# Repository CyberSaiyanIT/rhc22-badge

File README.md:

# RHC22 Badge

Cyber Saiyan community has designed and developed a special gadget to celebrate RomHack Camp 2022.

You can play with the badge during MOCA 2024 at Cyber Saiyan Village where we will have 20 badges available. If you have your own badge from RomHack Camp 2022 please bring it with you.
Some useful information
* In order to start playing around with and hacking it, is recommended to bring a micro USB data cable with you
* It is also recommended to bring replacement 1.5V AA batteries and/or a powerbank
* The badge is already flashed with the MOCA specific firmware
* We really will appreciate any improvement to the project and pull requests
* Don't hesitate to come and visit us at the Cyber Saiyan Village if you need help

## Features

The badge has some very simple features that will improve your Camp experience:
* It is designed to recall the dragon spheres (maybe you will be able to summon Shenron too)
* The base SOC is a single core ESP32-C3 
   * Integrates a 32-bit core RISC-V microcontroller with a maximum clock speed of 160 MHz
   * 22 configurable GPIOs
   * 400 KB of internal RAM and 4MB flash
   * WiFi and Bluetooth 5
* In the front there are 7 RGB leds
* In the back you have  
   * Two push buttons; use your nail for a better experience :)
   * A 2.4'' TFT screen 
   * A two AA battery holder

Once powered the badge will be assigned a 1-7 ID and will start to advertise itself using BLE and the screen will show the RomHack Camp 2022 logo 
* You can move to next/prev screen by a 1s long press
* The 1st screen is the RHC22 schedule: 
   * You will be able to read the schedule of the Camp (use the 4th screen to update it)
* The 2nd screen is the badges' radar: 
   * You will see all the badges around you in a dragon ball style
* The 3rd screen is the badge's list: 
   * You will see all the badges around you in a table view
* The 4th screen is for the WiFI functionalities: 
   * Start the AP mode and connect with your PC/smartphone in order to explore more functionalities
   * Start the schedule SYNC mode in order to update the schedule at the 2nd screen
* The 5th screen is for fun (you will be able to play with snake)

# Toolchain setup

## Prepare the environment 

### Visual Studio Code (VSCode)
Install Visual Studio Code as development environment:

* https://code.visualstudio.com/ - follow instructions there, if you don't have vscode yet.

### PlatformIO (PIO) extension
Install PlatformIO extension on Visual Studio Code:

* [Installation](http://docs.platformio.org/page/ide/vscode.html)
* [Quick Start](http://docs.platformio.org/page/ide/vscode.html#quick-start)
* [User Guide](http://docs.platformio.org/page/ide/vscode.html#user-guide)

Please follow to the official documentation [PlatformIO IDE for VSCode](http://docs.platformio.org/page/ide/vscode.html).

## Setup the project

* Git clone this repository and open it on VSCode

If you get the error message "No module named pkg_resources", you need to open the 'PlatformIO Core CLI' and execute command:
   * <span>pip install setuptools</span>

## Build www data (Linux)

* Prerequisites:
   * Install Node.js and NPM
* Use NPM to Install required Packages:
   * npm install node-minify node-sass

* ./www-build.sh

## Build www data (Docker)

* Install docker
* docker build --pull --rm -f "Dockerfile" -t rhc22badge:latest "."
* (Bash) docker run -it -v <span>$</span>(pwd)/public:/public -v <span>$</span>(pwd)/data/www:/output rhc22badge
* (Powershell) docker run -it -v <span>$</span>{PWD}/public:/public -v <span>$</span>{PWD}/data/www:/output rhc22badge
   
## Build/Upload Filesystem

In order to upload the filesystem to the badge you need to plugin the badge using USB.
In the "Project Tasks" view of PIO navigate to:

* RHC22-Bagde
   * Platform
      * Build Filesystem Image
      * Upload Filesystem Image

## Build/Upload Firmware
In order to upload the firmware to the badge you need to plugin the badge using USB.
In the "Project Tasks" view of PIO navigate to:

* RHC22-Bagde
   * General
      * Build
      * Upload

# Known Issues
* after dowloading the MOCA schedule from web you should restart the badge to see the updated schedule. This is due to a memory allocartion problem (the json file is too big) and the fix is a WIP

# Misc

## WiFi SSID name lenght limit

The WiFi SSID name configure to connect to external AP is limited to 20 chars

## Use a different logo image

To use a different logo first you need to 
* convert the BMP/JPG/PNG/SVG file to a C array; you can do this using an [online image converter](https://lvgl.io/tools/imageconverter) setting CF_TRUE_COLOR_ALPHA option
* adjust [main/badge/common/img_logo.c](main/badge/common/img_logo.c) file

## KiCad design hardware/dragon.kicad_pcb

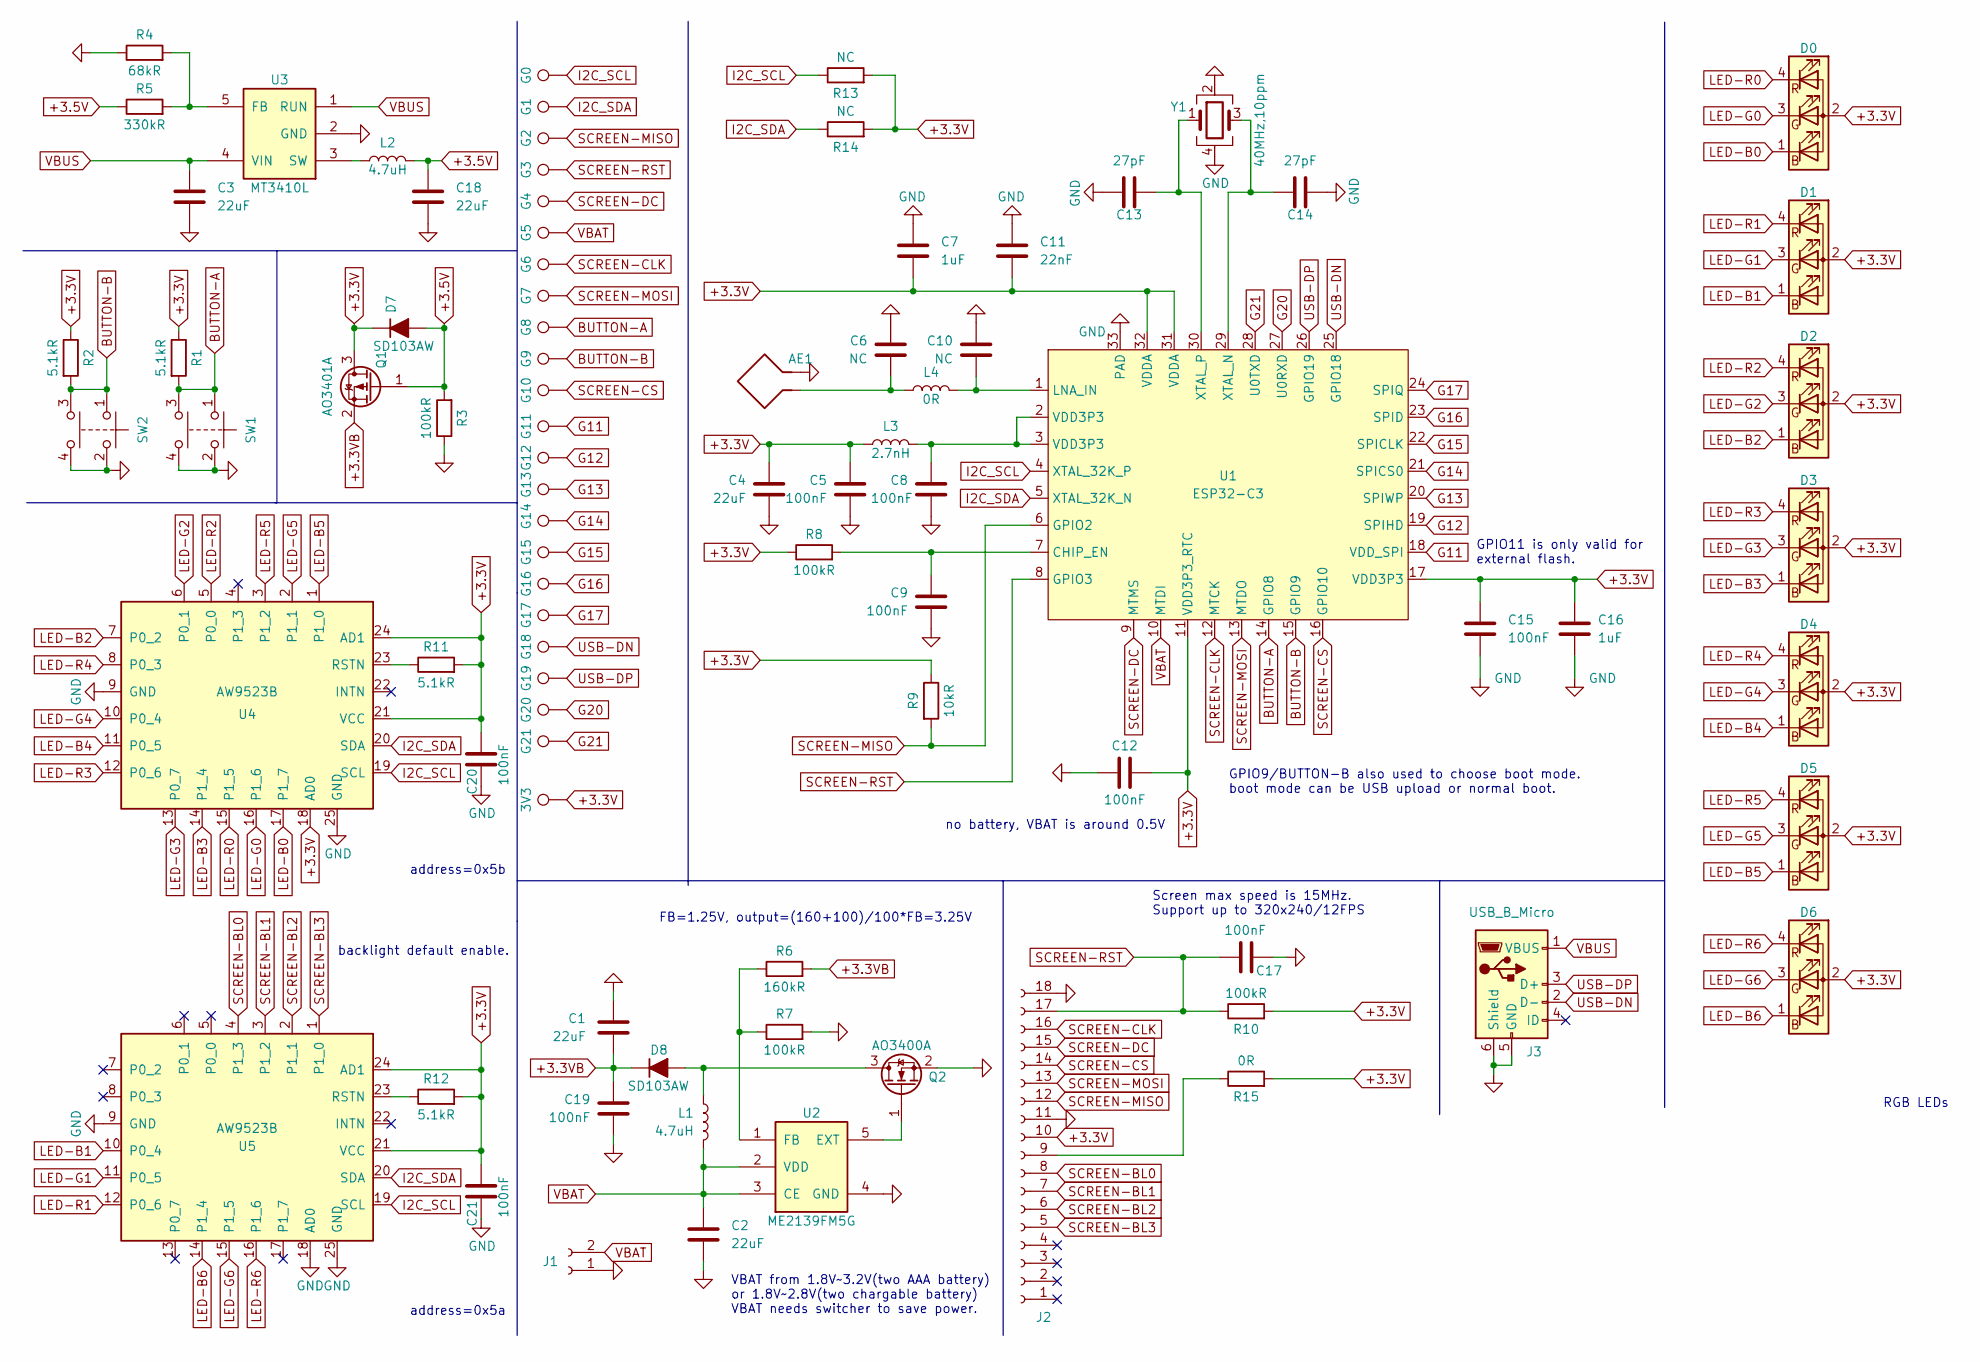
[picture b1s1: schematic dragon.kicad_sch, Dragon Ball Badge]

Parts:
3V3: TestPoint; TestPoint_Pad_D1.0mm
AE1: Antenna_Loop; Texas_SWRA117D_2.4GHz_Left
C1, C2, C3, C4, C18: 22uF; C_0603_1608Metric
C5, C8, C9, C12, C15, C17, C19, C20, C21: 100nF; C_0402_1005Metric
C6, C10: NC; C_0402_1005Metric
C7, C16: 1uF; C_0402_1005Metric
C11: 22nF; C_0402_1005Metric
C13, C14: 27pF; C_0402_1005Metric
D0, D1, D2, D3, D4, D5, D6: LED_BAGR
D7, D8: SD103AW; D_SOD-123
G0, G1, G2, G3, G4, G5, G6, G7, G8, G9, G10, G11, G12, G13, G14, G15, G16, G17, G18, G19, G20, G21: TestPoint; TestPoint_Pad_D1.0mm
J1: Conn_01x02_Female; PinSocket_1x02_P2.54mm_Vertical
J2: SCREEN; Hirose_FH12-18S-0.5SH_1x18-1MP_P0.50mm_Horizontal
J3: USB_B_Micro; USB_Micro-B
L1, L2: 4.7uH; L_1008_2520Metric
L3: 2.7nH; L_0402_1005Metric
L4: 0R; L_0402_1005Metric
Q1: AO3401A; SOT-23
Q2: AO3400A; SOT-23
R1, R2, R11, R12: 5.1kR; R_0402_1005Metric
R3, R7, R8, R10: 100kR; R_0402_1005Metric
R4: 68kR; R_0402_1005Metric
R5: 330kR; R_0402_1005Metric
R6: 160kR; R_0402_1005Metric
R9: 10kR; R_0402_1005Metric
R13, R14: NC; R_0402_1005Metric
R15: 0R; R_0402_1005Metric
SW1, SW2: SW_Push_Dual; BUTTON
U1: ESP32-C3; QFN-32-1EP_5x5mm_P0.5mm_EP3.1x3.1mm
U2: ME2139FM5G; SOT-23-5
U3: MT3410L; SOT-23-5
U4, U5: AW9523B; HVQFN-24-1EP_4x4mm_P0.5mm_EP2.6x2.6mm
Y1: 40MHz,10ppm; Crystal_SMD_3225-4Pin_3.2x2.5mm

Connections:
+3.3V: 3V3.1, C4.2, C5.2, C7.1, C11.1, C12.1, C15.2, C16.2, C20.2, C21.2, D0.2 (A), D1.2 (A), D2.2 (A), D3.2 (A), D4.2 (A), D5.2 (A), D6.2 (A), D7.1 (K), J2.10, L3.1, Q1.3 (D), R1.1, R2.1, R8.1, R9.1, R10.2, R11.2, R12.2, R13.2, R14.2, R15.2, U1.11 (VDD3P3_RTC), U1.17 (VDD3P3), U1.31 (VDDA), U1.32 (VDDA), U4.18 (AD0), U4.21 (VCC), U4.24 (AD1), U5.21 (VCC), U5.24 (AD1)
+3.3VB: C1.1, C19.2, D8.1 (K), Q1.2 (S), R6.2
+3.5V: C18.1, D7.2 (A), L2.2, Q1.1 (G), R3.2, R5.1
BUTTON-A: G8.1, R1.2, SW1.1, SW1.3, U1.14 (GPIO8)
BUTTON-B: G9.1, R2.2, SW2.1, SW2.3, U1.15 (GPIO9)
G11: G11.1, U1.18 (VDD_SPI)
G12: G12.1, U1.19 (SPIHD)
G13: G13.1, U1.20 (SPIWP)
G14: G14.1, U1.21 (SPICS0)
G15: G15.1, U1.22 (SPICLK)
G16: G16.1, U1.23 (SPID)
G17: G17.1, U1.24 (SPIQ)
G20: G20.1, U1.27 (U0RXD)
G21: G21.1, U1.28 (U0TXD)
GND: AE1.2, C1.2, C2.2, C3.2, C4.1, C5.1, C6.2, C7.2, C8.1, C9.1, C10.2, C11.2, C12.2, C13.1, C14.2, C15.1, C16.1, C17.2, C18.2, C19.1, C20.1, C21.1, J1.1, J2.11, J2.18, J3.5 (GND), J3.6 (Shield), Q2.2 (S), R3.1, R4.1, R7.2, SW1.2, SW1.4, SW2.2, SW2.4, U1.33 (PAD), U2.4 (GND), U3.2 (GND), U4.9 (GND), U4.25 (GND), U5.9 (GND), U5.18 (AD0), U5.25 (GND), Y1.2, Y1.4; also elsewhere on the board
I2C_SCL: G0.1, R13.1, U1.4 (XTAL_32K_P), U4.19 (SCL), U5.19 (SCL)
I2C_SDA: G1.1, R14.1, U1.5 (XTAL_32K_N), U4.20 (SDA), U5.20 (SDA)
LED-B0: D0.1 (BK), U4.17 (P1_7)
LED-B1: D1.1 (BK), U5.10 (P0_4)
LED-B2: D2.1 (BK), U4.7 (P0_2)
LED-B3: D3.1 (BK), U4.14 (P1_4)
LED-B4: D4.1 (BK), U4.11 (P0_5)
LED-B5: D5.1 (BK), U4.1 (P1_0)
LED-B6: D6.1 (BK), U5.14 (P1_4)
LED-G0: D0.3 (GK), U4.16 (P1_6)
LED-G1: D1.3 (GK), U5.11 (P0_5)
LED-G2: D2.3 (GK), U4.6 (P0_1)
LED-G3: D3.3 (GK), U4.13 (P0_7)
LED-G4: D4.3 (GK), U4.10 (P0_4)
LED-G5: D5.3 (GK), U4.2 (P1_1)
LED-G6: D6.3 (GK), U5.15 (P1_5)
LED-R0: D0.4 (RK), U4.15 (P1_5)
LED-R1: D1.4 (RK), U5.12 (P0_6)
LED-R2: D2.4 (RK), U4.5 (P0_0)
LED-R3: D3.4 (RK), U4.12 (P0_6)
LED-R4: D4.4 (RK), U4.8 (P0_3)
LED-R5: D5.4 (RK), U4.3 (P1_2)
LED-R6: D6.4 (RK), U5.16 (P1_6)
unnamed: AE1.1, C6.1, L4.1
unnamed: C8.2, L3.2, U1.2 (VDD3P3), U1.3 (VDD3P3)
unnamed: C9.2, R8.2, U1.7 (CHIP_EN)
unnamed: C10.1, L4.2, U1.1 (LNA_IN)
unnamed: C13.2, U1.30 (XTAL_P), Y1.1
unnamed: C14.1, U1.29 (XTAL_N), Y1.3
unnamed: D8.2 (A), L1.2, Q2.3 (D)
unnamed: J2.9, R15.1
unnamed: L2.1, U3.3 (SW)
unnamed: Q2.1 (G), U2.5 (EXT)
unnamed: R4.2, R5.2, U3.5 (FB)
unnamed: R6.1, R7.1, U2.1 (FB)
unnamed: R11.1, U4.23 (RSTN)
unnamed: R12.1, U5.23 (RSTN)
SCREEN-BL0: J2.8, U5.4 (P1_3)
SCREEN-BL1: J2.7, U5.3 (P1_2)
SCREEN-BL2: J2.6, U5.2 (P1_1)
SCREEN-BL3: J2.5, U5.1 (P1_0)
SCREEN-CLK: G6.1, J2.16, U1.12 (MTCK)
SCREEN-CS: G10.1, J2.14, U1.16 (GPIO10)
SCREEN-DC: G4.1, J2.15, U1.9 (MTMS)
SCREEN-MISO: G2.1, J2.12, R9.2, U1.6 (GPIO2)
SCREEN-MOSI: G7.1, J2.13, U1.13 (MTDO)
SCREEN-RST: C17.1, G3.1, J2.17, R10.1, U1.8 (GPIO3)
USB-DN: G18.1, J3.2 (D-), U1.25 (GPIO18)
USB-DP: G19.1, J3.3 (D+), U1.26 (GPIO19)
VBAT: C2.1, G5.1, J1.2, L1.1, U1.10 (MTDI), U2.2 (VDD), U2.3 (CE)
VBUS: C3.1, J3.1 (VBUS), U3.1 (RUN), U3.4 (VIN)

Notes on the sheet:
RGB LEDs
VBAT from 1.8V~3.2V(two AAA battery) or 1.8V~2.8V(two chargable battery) VBAT needs switcher to save power.
Screen max speed is 15MHz. Support up to 320x240/12FPS
FB=1.25V, output=(160+100)/100*FB=3.25V
no battery, VBAT is around 0.5V
GPIO9/BUTTON-B also used to choose boot mode. boot mode can be USB upload or normal boot.
address=0x5b
backlight default enable.
address=0x5a
GPIO11 is only valid for external flash.

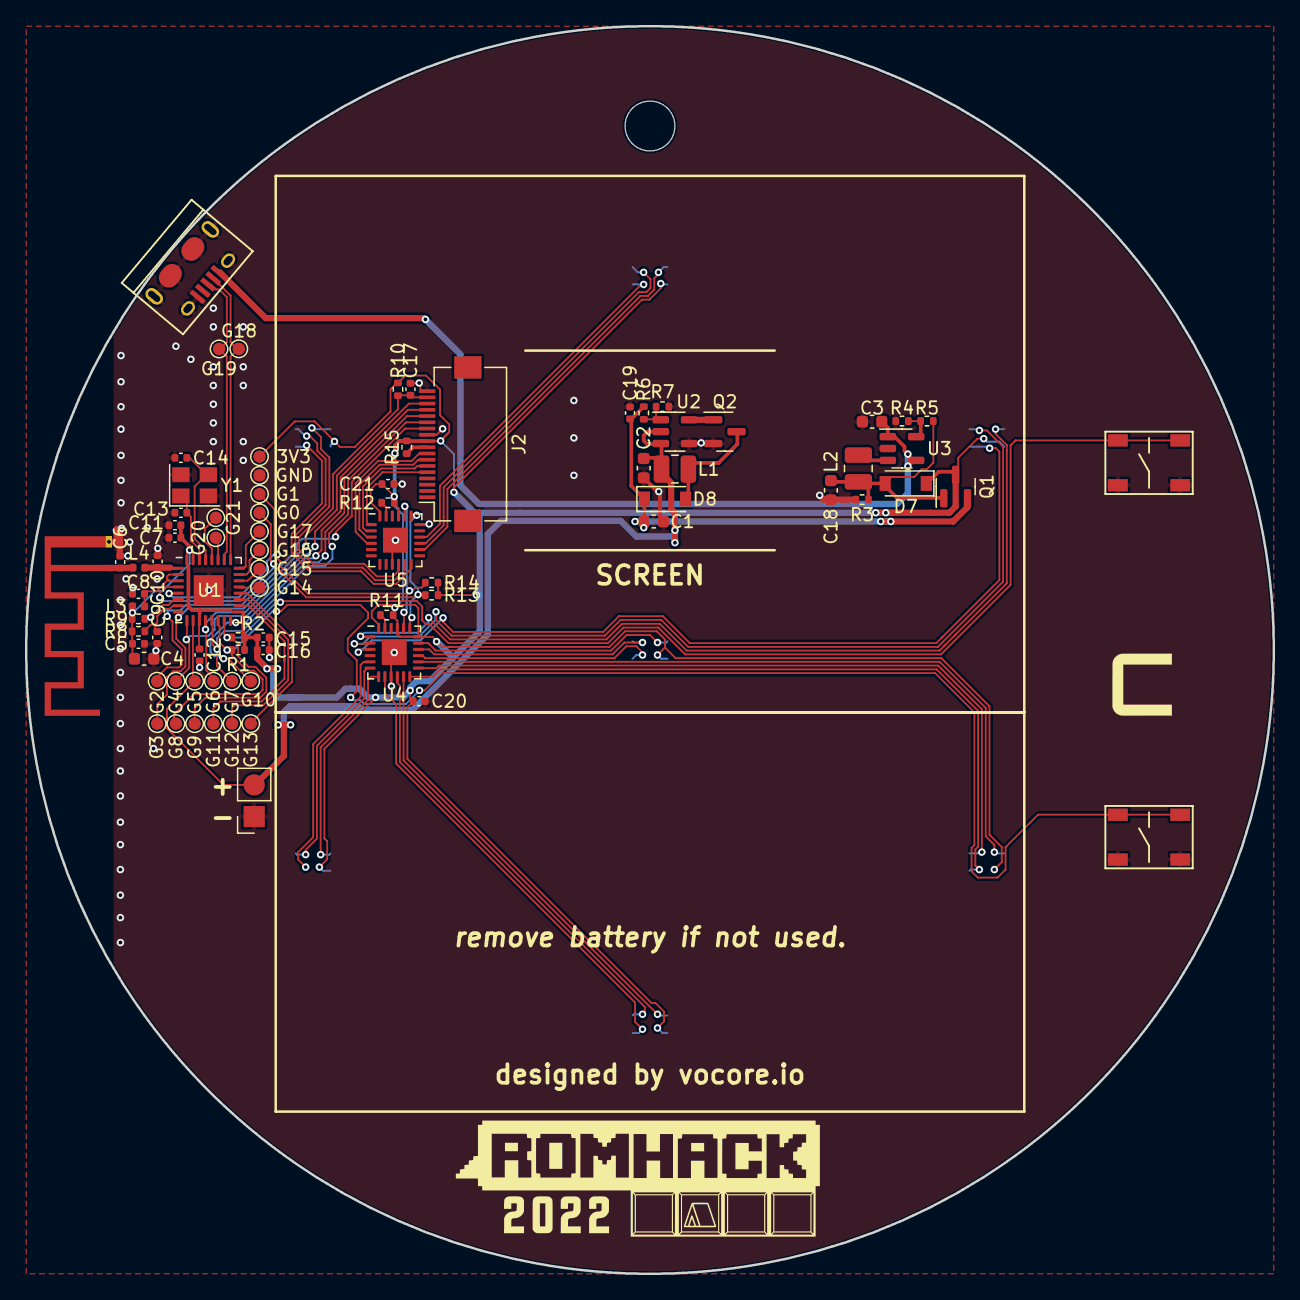
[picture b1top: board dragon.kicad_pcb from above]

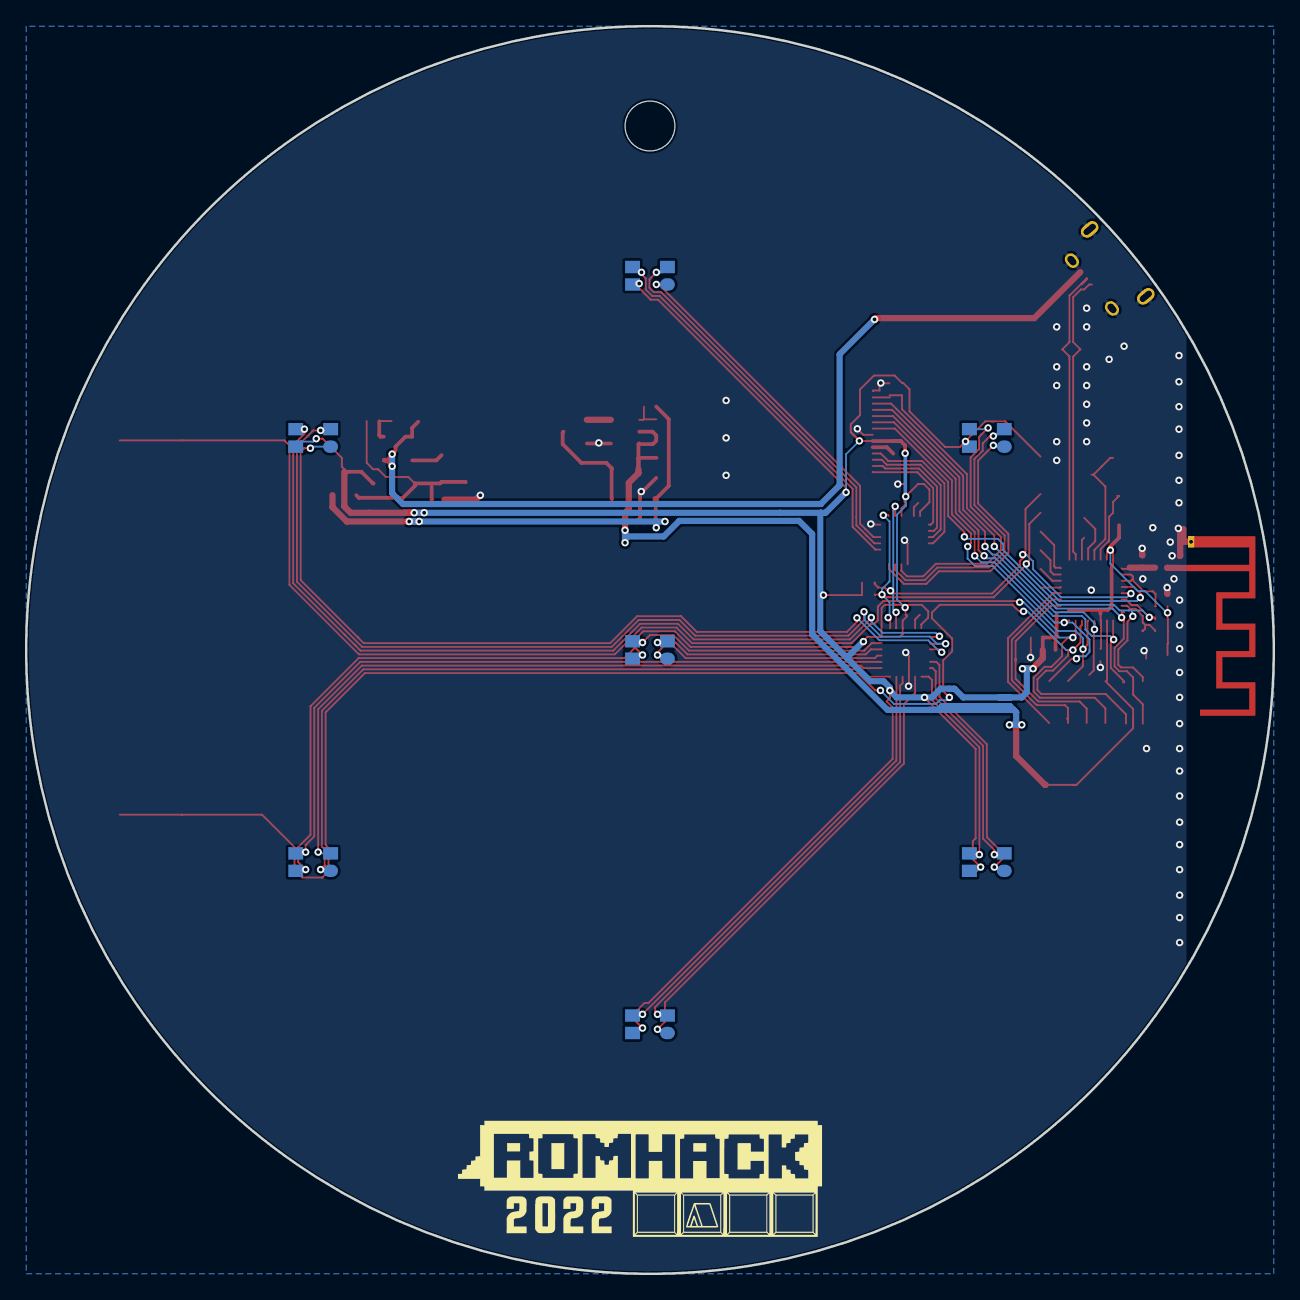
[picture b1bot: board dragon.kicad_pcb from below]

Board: 2 copper layers, 100.0 x 100.0 mm, 87 parts (7 on the bottom side), 66 nets.

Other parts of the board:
GND: TestPoint; TestPoint_Pad_D1.0mm

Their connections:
GND: GND.1; also elsewhere on the board

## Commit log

2022-09-19 READE Updates
    Minor fixes
2022-09-19 Update README.md
    sed s/Functionalities/Features
2022-09-23 Update badge.c
    fixed bug where the check for the 7 spheres always fail because only check the first sphere (ble_nodes->id instead of ble_nodes[i].id)
2022-09-26 Create LICENSE
2022-09-27 fix #2
2022-09-27 Dockerfile and instruction to build www
2023-09-09 Customize badge firmware for ESC 2023 - reset wifi ssid&pwd - add ESC 2023 schedule to local fs - change logo to ESC logo - change sync url
2023-09-11 Use a different logo image
    README updated
2024-08-08 Fix ESP-IDF platform version
2024-08-10 Fix for ESP platform version 5.4.0
2024-08-10 Customize badge firmware for MOCA 2024 - reset wifi ssid&pwd - add MOCA 2024 schedule to local fs [WIP] - change logo to MOCA logo - change sync url Update - added logo background color
2024-08-30 Fix display large Event table
2024-09-01 Fix build flags and don't clear failed sync schedule
2024-09-05 Add Known Issues section
2024-09-05 Update SSID and pwd
    Reported some connection problem due to special chars
2024-09-06 Correct prefixing sound of FREKETE
    In the Abruzzese dialect the prefixing sound often emitted before the
    "freghete" (or, hardened, "frekete") exclamation is the Short-o-2 (aka
    Alternate-Short-o). To pronounce this sound clearly, the lips should NOT be
    rounded, the tongue should be very relaxed in the middle of the mouth, and the
    mouth is less open than for regular Short-o. Its emission can also diverge for
    the Schwa sound in some cases: the prefix is not stressed, but never completely
2024-09-06 Change SSID name
    SSIDs longer that 20 chars won't work, reduce the SSID size
2024-09-06 Readme update
    - MOCA specific information
    - WiFi SSID limit
2024-09-06 Updated ReadMe installation instructions
2024-09-07 Fix script to build www data on Linux
2024-09-18 moca2024: best firmware hack commit
    Actually this commit disable the wifi and bt initialization (more cleanup needed); add the business login to randomize the 'magic' answer; add some images as 'magic' answers (later will be converted 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
